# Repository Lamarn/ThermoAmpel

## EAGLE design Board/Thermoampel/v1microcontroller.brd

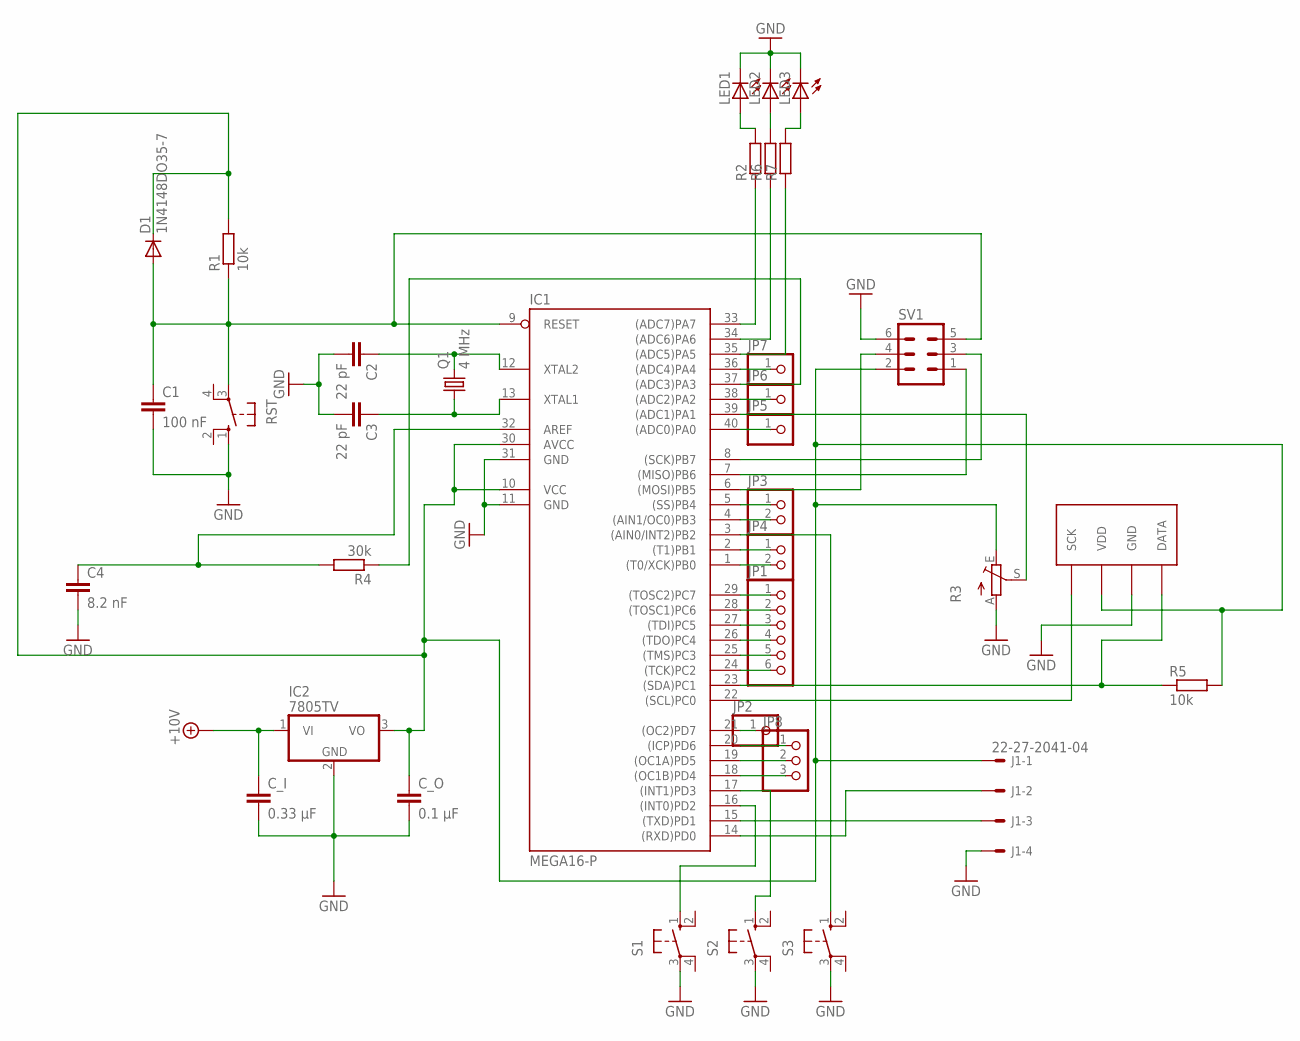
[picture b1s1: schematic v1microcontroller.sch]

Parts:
C1: 100 nF; C2.5-3
C2, C3: 22 pF; C2.5-3
C4: 8.2 nF; C2.5-3
C_I: 0.33 μF; C2.5-3
C_O: 0.1 μF; C2.5-3
D1: 1N4148DO35-7; DO35-7
IC1: MEGA16-P; DIL40
IC2: 7805TV; TO220V
J1: 22-27-2041-04; 6410-04
JP1: PINHD-1X6; 1X06
JP2, JP5, JP6, JP7: PINHD-1X1; 1X01
JP3, JP4: PINHD-1X2; 1X02
JP8: PINHD-1X3; 1X03
LED1, LED2, LED3: LED5MM
Q1: 4 MHz; HC49U-V
R1, R5: 10k; 0204/5
R2, R6, R7: R-EU_0204/5; 0204/5
R3: TRIM_EU-CT6; CT6
R4: 30k; 0204/5
RST: 10-XX; B3F-10XX
S1, S2, S3: 10-XX; B3F-10XX
SV1: ML6
U$1: SHT71; SHT7X

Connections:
+10V: C_I.1, IC2.1 (VI)
GND: C1.2, C2.2, C3.2, C4.2, C_I.2, C_O.2, IC1.11 (GND), IC1.31 (GND), IC2.2 (GND), J1.4, LED1.K (C), LED2.K (C), LED3.K (C), R3.A, RST.1 (S), S1.3, S2.3, S3.3, SV1.6, U$1.3 (GND)
unnamed: C1.1, D1.A, IC1.9 (RESET), R1.1, RST.3, SV1.5
unnamed: LED3.A, R7.2
unnamed: C_O.1, D1.C, IC1.10 (VCC), IC1.30 (AVCC), IC2.3 (VO), J1.1, R1.2, R3.E, R5.2, SV1.2, U$1.2 (VDD)
unnamed: IC1.33 ((ADC7)PA7), R2.1
unnamed: IC1.7 ((MISO)PB6), SV1.1
unnamed: IC1.6 ((MOSI)PB5), SV1.4
unnamed: LED2.A, R6.2
unnamed: C2.1, IC1.12 (XTAL2), Q1.2
unnamed: C3.1, IC1.13 (XTAL1), Q1.1
unnamed: IC1.39 ((ADC1)PA1), R3.S
unnamed: LED1.A, R2.2
unnamed: IC1.21 ((OC2)PD7), JP2.1
unnamed: C4.1, IC1.32 (AREF), R4.2
unnamed: IC1.8 ((SCK)PB7), SV1.3
unnamed: IC1.20 ((ICP)PD6), JP8.1
unnamed: IC1.19 ((OC1A)PD5), JP8.2
unnamed: IC1.18 ((OC1B)PD4), JP8.3
unnamed: IC1.29 ((TOSC2)PC7), JP1.1
unnamed: IC1.15 ((TXD)PD1), J1.3
unnamed: IC1.14 ((RXD)PD0), J1.2
unnamed: IC1.16 ((INT0)PD2), S1.1 (S)
unnamed: IC1.17 ((INT1)PD3), S2.1 (S)
unnamed: IC1.3 ((AIN0/INT2)PB2), S3.1 (S)
unnamed: IC1.22 ((SCL)PC0), U$1.1 (SCK)
unnamed: IC1.23 ((SDA)PC1), R5.1, U$1.4 (DATA)
unnamed: IC1.28 ((TOSC1)PC6), JP1.2
unnamed: IC1.27 ((TDI)PC5), JP1.3
unnamed: IC1.26 ((TDO)PC4), JP1.4
unnamed: IC1.25 ((TMS)PC3), JP1.5
unnamed: IC1.24 ((TCK)PC2), JP1.6
unnamed: IC1.5 ((SS)PB4), JP3.1
unnamed: IC1.4 ((AIN1/OC0)PB3), JP3.2
unnamed: IC1.2 ((T1)PB1), JP4.1
unnamed: IC1.1 ((T0/XCK)PB0), JP4.2
unnamed: IC1.34 ((ADC6)PA6), R6.1
unnamed: IC1.35 ((ADC5)PA5), R7.1
unnamed: IC1.40 ((ADC0)PA0), JP5.1
unnamed: IC1.37 ((ADC3)PA3), R4.1
unnamed: IC1.38 ((ADC2)PA2), JP6.1
unnamed: IC1.36 ((ADC4)PA4), JP7.1

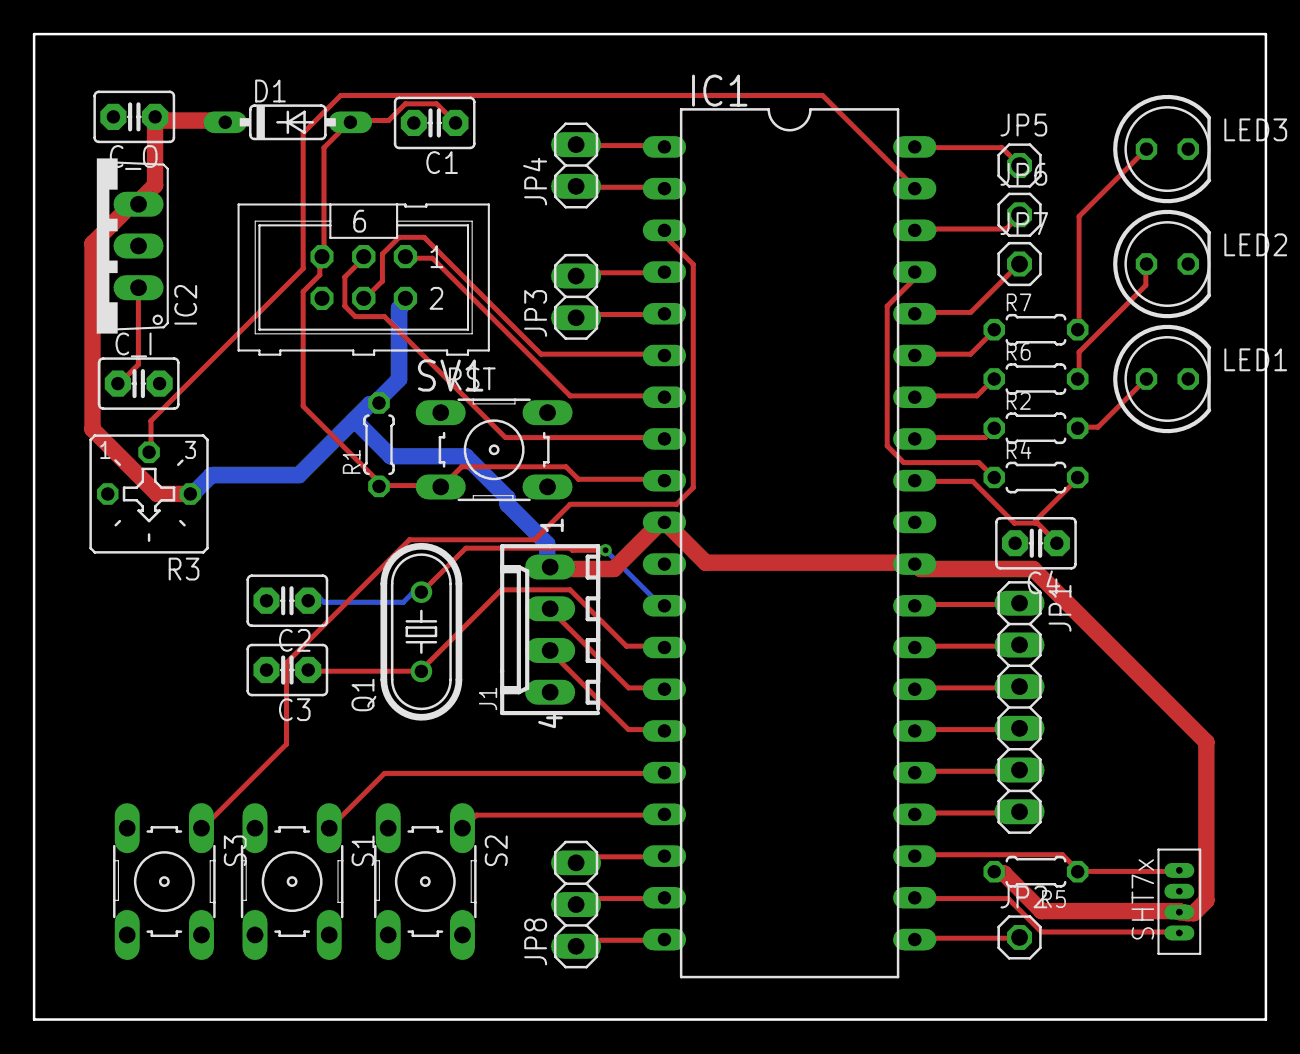
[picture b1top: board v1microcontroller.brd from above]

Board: 2 copper layers, 75.0 x 60.0 mm, 35 parts (0 on the bottom side), 42 nets.

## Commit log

2018-09-18 further changes
2018-09-18 some cleanup of code
2018-09-18 LED bugfix: Internen pullup resistor aktiviert
2018-09-19 Routine für Delay von 500ms hinzugefügt, realisiert über 16-Bit Timer/Counter
2018-09-21 Eigentlich fertiger Code für TWI, aber festgestellt, dass Sensor das nicht unterstützt!
2018-09-23 - Kommunikation mit dem Sensor jetzt möglich - TWI Routine ausgelagert
2018-09-23 1) Leuchten der LEDs bedeutet jetzt Folgendes: - Rote LED: RH ist kleiner als 40 oder größer als 60 - Gelbe LED: Temperatur ist jetzt kleiner als 20°C oder größer als 23°C - Grüne LED: Beide Werte si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
    2) Code etwas verbessert und aufgeräumt.
2018-10-01 LUT für Umwandlung von Sensordaten hinzugefügt
2018-10-10 UART communication implemented, Interrupt tweaks
2018-10-14 gitignore angepasst für das Eagle Projekt
2018-10-14 Board Projektdateien hinzugefügt
2018-10-14 gitignore für Latex angepasst
2018-10-14 Dateien angelegt für die Dokumentation
2018-10-18 Dokumentation: weitere Aspekte in Stichpunkten hinzugefügt
2018-10-26 Erster Text in der Zeit bei der Arbeit wo ich den Rechner nicht hatte xD
2018-11-26 Softwareaspekt der Dokumentation weiter ausgeführt
2018-11-26 Mehr Struktur im Softwarepart reingebracht und Sachen ergänzt, paar Aspekte sind noch offen.
2018-11-29 Abschnitt "Funktionsweise der Software" fertig
2018-12-03 Finale Änderungen an der Dokumentation
2018-12-04 Interrupts gefixt
2018-12-05 Bugfix bei Timer0_Interrupt
2018-12-05 Interruptteil aktualisiert. Finale Version!
2018-12-05 Interruptteil aktualisiert. Finale Version (dieses mal ganz sicher!)
2019-07-16 push of some changes?
